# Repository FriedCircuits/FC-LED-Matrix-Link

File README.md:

FC-LED-Matrix-Link
================

This is the design files for the LED Matrix Link

Hardware available on [https://www.tindie.com/stores/FriedCircuits/](https://www.tindie.com/stores/FriedCircuits/)

More info can be found on [http://friedcircuits.us/docs/led-matrix/led-matrix-link/](http://friedcircuits.us/docs/led-matrix/led-matrix-link/)

Scrolling text example for Due - [https://github.com/FriedCircuits/LED_Twitter_Due](https://github.com/FriedCircuits/LED_Twitter_Due)

I will add more examples here over time.

License: All source code and designs are released under 

Creative Commons NonCommercial-ShareAlike 

CC BY-NC-SA

Please contact me for commercial opportunities.

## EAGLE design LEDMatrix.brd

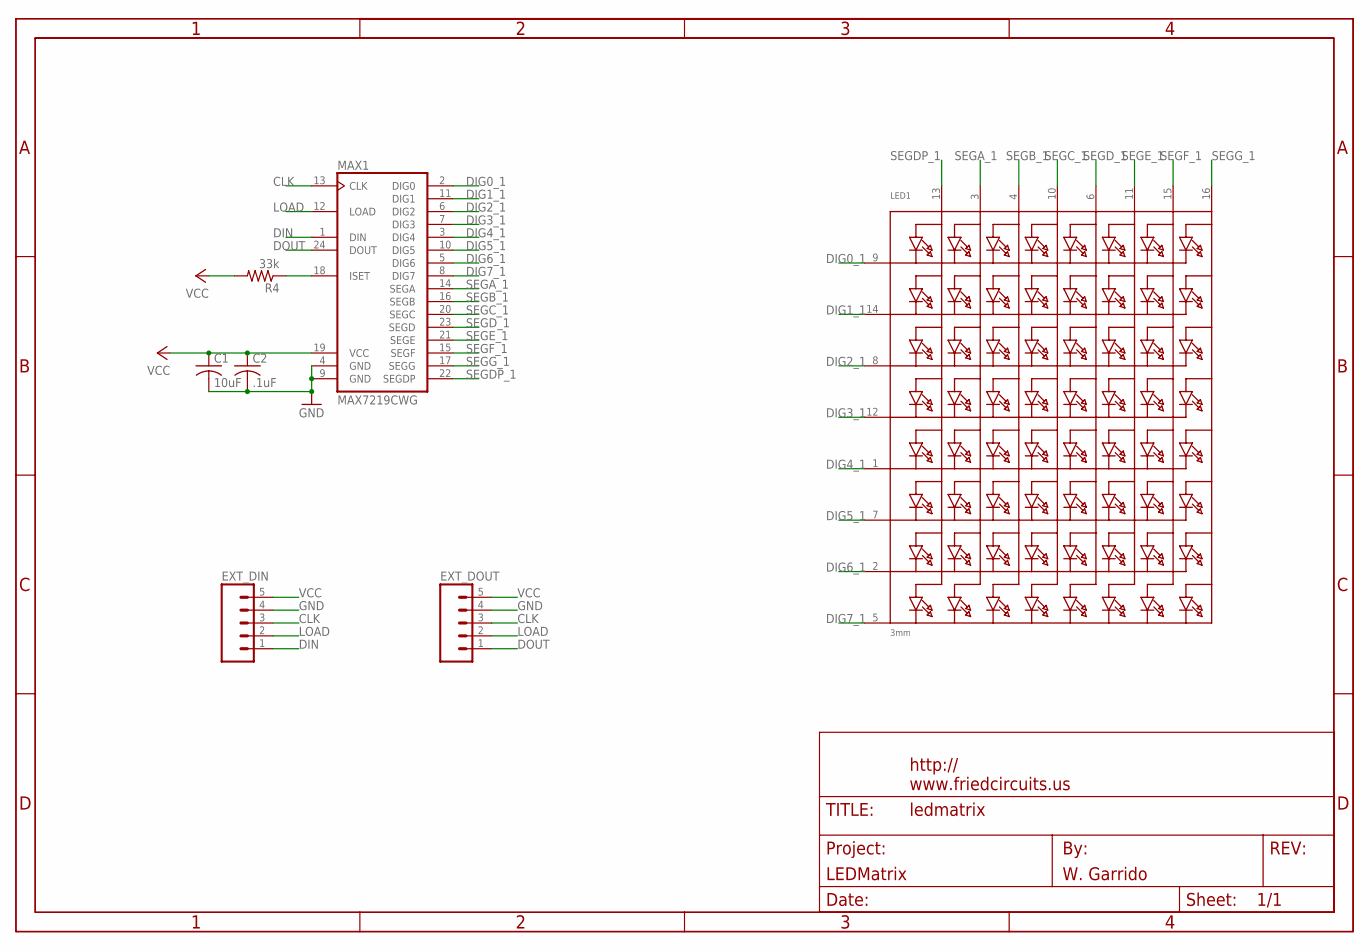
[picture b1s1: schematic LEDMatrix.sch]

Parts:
C1: 10uF; C0805
C2: .1uF; C0805
EXT_DIN: M05LOCK_LONGPADS; 1X05_LOCK_LONGPADS
EXT_DOUT: M05LOCK_LONGPADS; 1X05_LOCK_LONGPADS
LED1: 3mm; SEGMENT_BL-M12A881UR
MAX1: MAX7219CWG; SO24W
R4: 33k; M0805
U$1: FRAME_DINA4_L; FC_CREDIT

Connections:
CLK: EXT_DIN.3, EXT_DOUT.3, MAX1.13 (CLK)
DIG0_1: LED1.9 (K1), MAX1.2 (DIG0)
DIG1_1: LED1.14 (K2), MAX1.11 (DIG1)
DIG2_1: LED1.8 (K3), MAX1.6 (DIG2)
DIG3_1: LED1.12 (K4), MAX1.7 (DIG3)
DIG4_1: LED1.1 (K5), MAX1.3 (DIG4)
DIG5_1: LED1.7 (K6), MAX1.10 (DIG5)
DIG6_1: LED1.2 (K7), MAX1.5 (DIG6)
DIG7_1: LED1.5 (K8), MAX1.8 (DIG7)
DIN: EXT_DIN.1, MAX1.1 (DIN)
DOUT: EXT_DOUT.1, MAX1.24 (DOUT)
GND: C1.2, C2.2, EXT_DIN.4, EXT_DOUT.4, MAX1.4 (GND), MAX1.9 (GND)
LOAD: EXT_DIN.2, EXT_DOUT.2, MAX1.12 (LOAD)
unnamed: MAX1.18 (ISET), R4.1
SEGA_1: LED1.3 (A2), MAX1.14 (SEGA)
SEGB_1: LED1.4 (A3), MAX1.16 (SEGB)
SEGC_1: LED1.10 (A4), MAX1.20 (SEGC)
SEGDP_1: LED1.13 (A1), MAX1.22 (SEGDP)
SEGD_1: LED1.6 (A5), MAX1.23 (SEGD)
SEGE_1: LED1.11 (A6), MAX1.21 (SEGE)
SEGF_1: LED1.15 (A7), MAX1.15 (SEGF)
SEGG_1: LED1.16 (A8), MAX1.17 (SEGG)
VCC: C1.1, C2.1, EXT_DIN.5, EXT_DOUT.5, MAX1.19 (VCC), R4.2

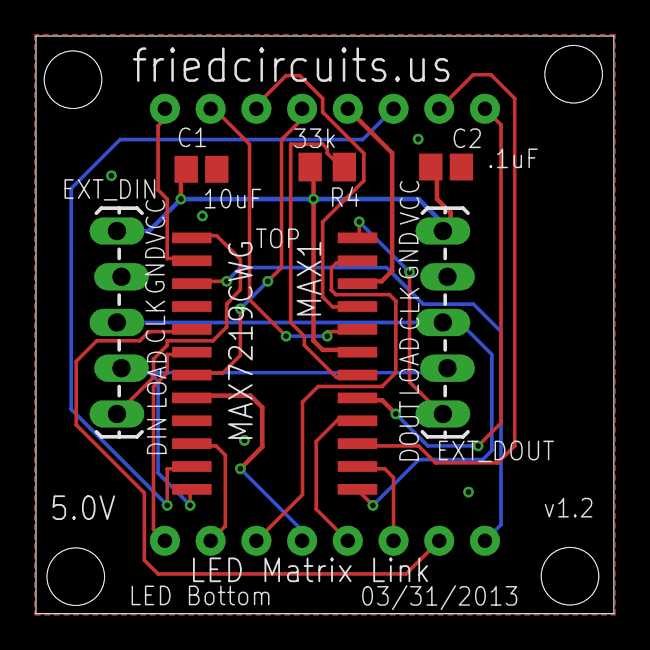
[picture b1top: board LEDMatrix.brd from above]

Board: 2 copper layers, 32.1 x 32.1 mm, 8 parts (1 on the bottom side), 23 nets.

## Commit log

2013-03-19 Initial readme file
2013-04-23 Added design files in Eagle and PNG

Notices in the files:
parts and their libraries:
SparkFun-Connectors: Licensing: CC v3.0 Share-Alike You are welcome to use this library for commercial purposes.
